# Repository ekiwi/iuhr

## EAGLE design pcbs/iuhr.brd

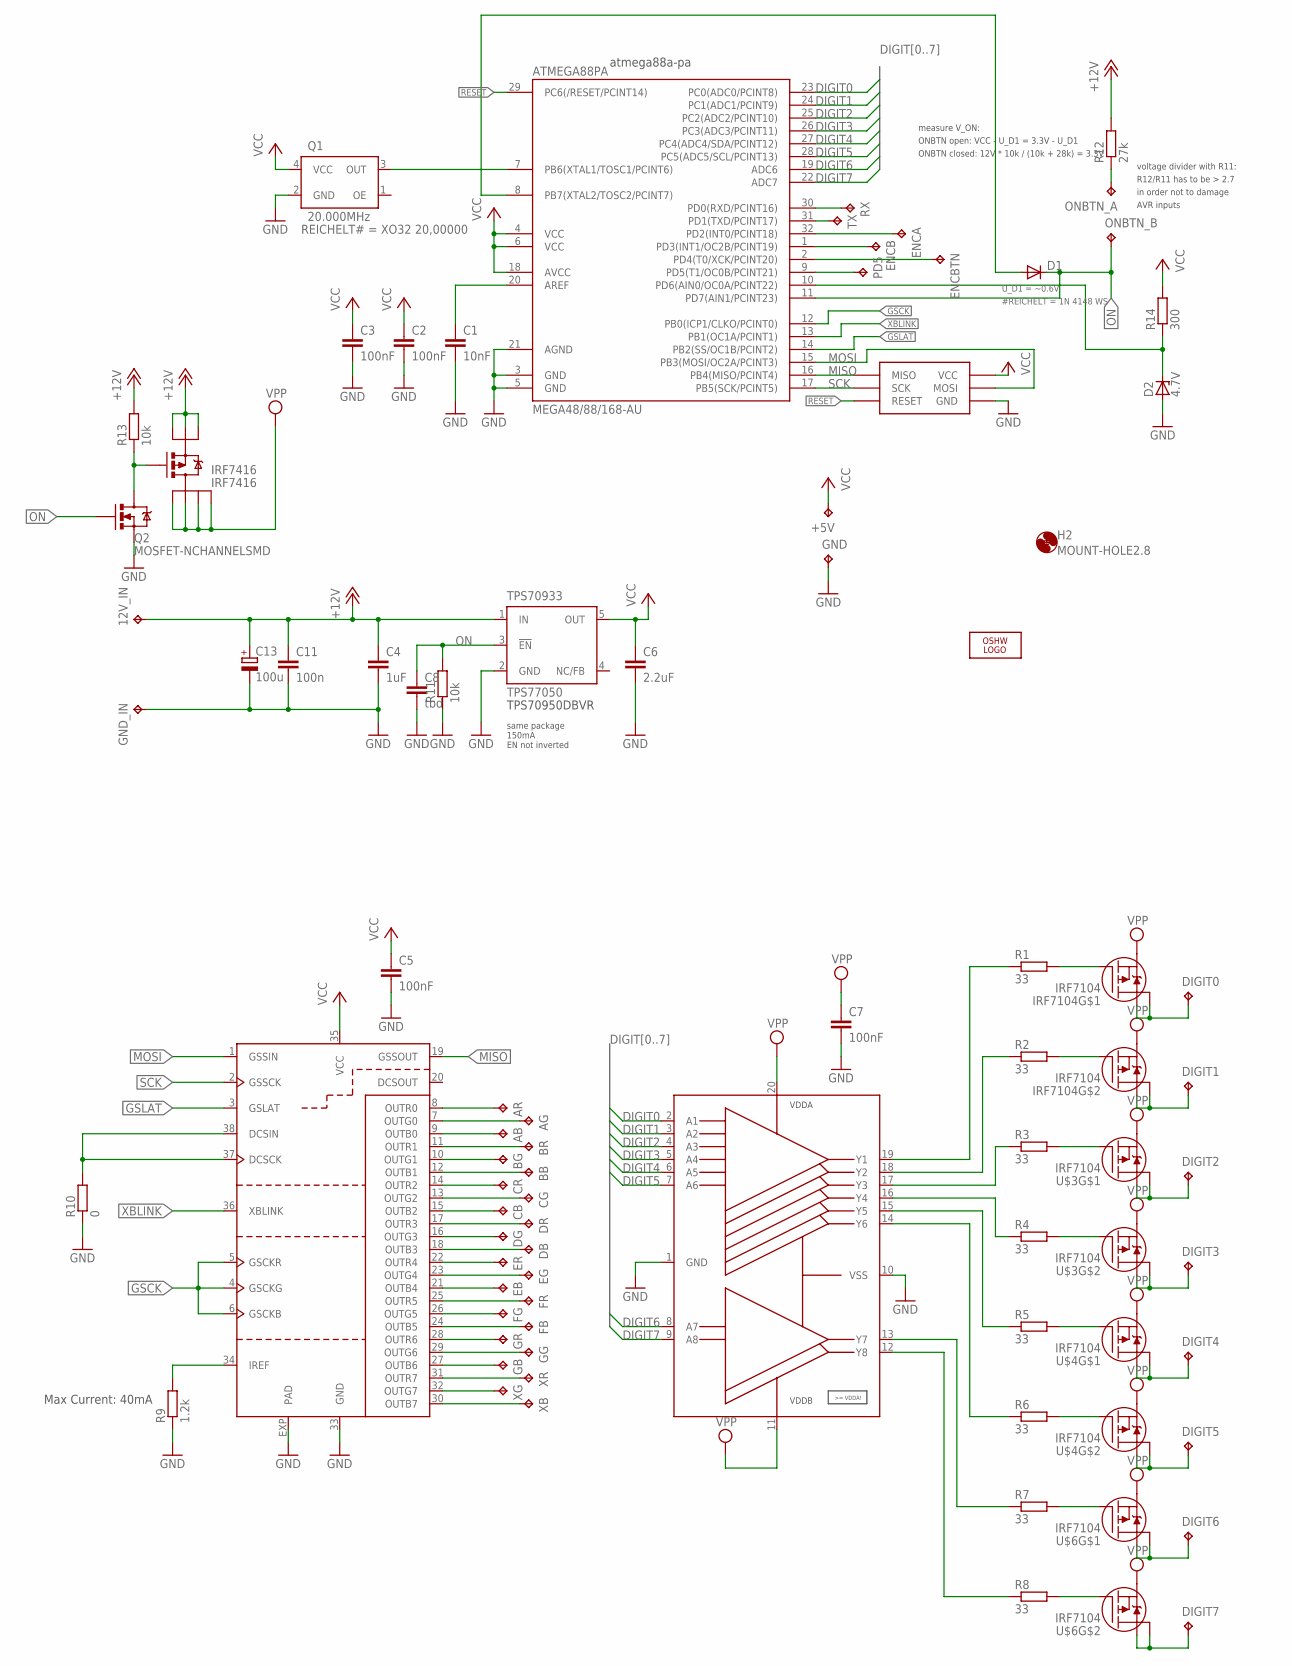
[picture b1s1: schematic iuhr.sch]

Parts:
12V_IN: TPTP20SQ; TP20SQ
+5V: TPTP15SQ; TP15SQ
AB: TPTP15SQ; TP15SQ
ADG3123: ADG3123BRUZ; TSSOP20
AG: TPTP15SQ; TP15SQ
AR: TPTP15SQ; TP15SQ
ATMEGA88PA: MEGA48/88/168-AU; TQFP32-08
BB: TPTP15SQ; TP15SQ
BG: TPTP15SQ; TP15SQ
BR: TPTP15SQ; TP15SQ
C1: 10nF; C0603
C2, C3, C5, C7: 100nF; C0603
C4: 1uF; C0805
C6: 2.2uF; C0805
C8: tbd; C0603
C11: 100n; C0603
C13: 100u; PANASONIC_E
CB: TPTP15SQ; TP15SQ
CG: TPTP15SQ; TP15SQ
CR: TPTP15SQ; TP15SQ
D1: DIODE-SOD323-R; SOD323-R
D2: 4.7V; SOT23
DB: TPTP15SQ; TP15SQ
DG: TPTP15SQ; TP15SQ
DIGIT0, DIGIT1, DIGIT2, DIGIT3, DIGIT4, DIGIT5, DIGIT6, DIGIT7: TPTP20SQ; TP20SQ
DR: TPTP15SQ; TP15SQ
EB: TPTP15SQ; TP15SQ
EG: TPTP15SQ; TP15SQ
ENCA: TPTP15SQ; TP15SQ
ENCB: TPTP15SQ; TP15SQ
ENCBTN: TPTP15SQ; TP15SQ
ER: TPTP15SQ; TP15SQ
FB: TPTP15SQ; TP15SQ
FG: TPTP15SQ; TP15SQ
FR: TPTP15SQ; TP15SQ
GB: TPTP15SQ; TP15SQ
GG: TPTP15SQ; TP15SQ
GND: TPTP15SQ; TP15SQ
GND_IN: TPTP20SQ; TP20SQ
GR: TPTP15SQ; TP15SQ
H2: MOUNT-HOLE2.8; 2,8
IRF7104: IRF7104; SO8-2
IRF7416: IRF7416; SO8-2
LOGO1: OSHW_LOGO_8MILX0200-NT; OSHW_8X200_NOTEXT
ONBTN_A: TPTP15SQ; TP15SQ
ONBTN_B: TPTP15SQ; TP15SQ
PD5: TPTP15SQ; TP15SQ
Q1: 20.000MHz; XO32
Q2: MOSFET-NCHANNELSMD; SOT23-3
R1, R2, R3, R4, R5, R6, R7, R8: 33; R0603
R9: 1.2k; R0603
R10: 0; R0603
R11, R13: 10k; R0603
R12: 27k; R0603
R14: 300; R0603
RX: TPTP15SQ; TP15SQ
TLC5951: TLC5951; HTSSOP38DAP
TPS70933: TPS77050; SOT23-DBV
TX: TPTP15SQ; TP15SQ
U$3, U$4, U$6: IRF7104; SO8-2
U$5: ISP_SPECIALS; ISP_RM2_00_STRAIGHT
XB: TPTP15SQ; TP15SQ
XG: TPTP15SQ; TP15SQ
XR: TPTP15SQ; TP15SQ

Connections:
+12V: 12V_IN.TP, C4.1, C11.1, C13.+, IRF7416.1 (S), IRF7416.2 (S1), IRF7416.3 (S2), R12.2, R13.2, TPS70933.1 (IN)
CLK_STM: ATMEGA88PA.7 (PB6(XTAL1/TOSC1/PCINT6)), Q1.3 (OUT)
DIGIT0: ADG3123.2 (A1), ATMEGA88PA.23 (PC0(ADC0/PCINT8))
DIGIT1: ADG3123.3 (A2), ATMEGA88PA.24 (PC1(ADC1/PCINT9))
DIGIT2: ADG3123.4 (A3), ATMEGA88PA.25 (PC2(ADC2/PCINT10))
DIGIT3: ADG3123.5 (A4), ATMEGA88PA.26 (PC3(ADC3/PCINT11))
DIGIT4: ADG3123.6 (A5), ATMEGA88PA.27 (PC4(ADC4/SDA/PCINT12))
DIGIT5: ADG3123.7 (A6), ATMEGA88PA.28 (PC5(ADC5/SCL/PCINT13))
DIGIT6: ADG3123.8 (A7), ATMEGA88PA.19 (ADC6)
DIGIT7: ADG3123.9 (A8), ATMEGA88PA.22 (ADC7)
GND: ADG3123.1 (GND), ADG3123.10 (VSS), ATMEGA88PA.3 (GND), ATMEGA88PA.5 (GND), ATMEGA88PA.21 (AGND), C1.2, C2.2, C3.2, C4.2, C5.2, C6.2, C7.2, C8.2, C11.2, C13.-, D2.1 (A), GND.TP, GND_IN.TP, Q1.2 (GND), Q2.2 (S), R9.1, R10.1, R11.1, TLC5951.33 (GND), TLC5951.EXP (PAD), TPS70933.2 (GND), U$5.VCC (GND)
GSCK: ATMEGA88PA.12 (PB0(ICP1/CLKO/PCINT0)), TLC5951.4 (GSCKG), TLC5951.5 (GSCKR), TLC5951.6 (GSCKB)
GSLAT: ATMEGA88PA.14 (PB2(SS/OC1B/PCINT2)), TLC5951.3 (GSLAT)
MISO: ATMEGA88PA.16 (PB4(MISO/PCINT4)), TLC5951.19 (GSSOUT), U$5.RESET (MISO)
MOSI: ATMEGA88PA.15 (PB3(MOSI/OC2A/PCINT3)), TLC5951.1 (GSSIN), U$5.MOSI
unnamed: AR.TP, TLC5951.8 (OUTR0)
unnamed: ATMEGA88PA.20 (AREF), C1.1
unnamed: AG.TP, TLC5951.7 (OUTG0)
unnamed: AB.TP, TLC5951.9 (OUTB0)
unnamed: BR.TP, TLC5951.11 (OUTR1)
unnamed: BG.TP, TLC5951.10 (OUTG1)
unnamed: ATMEGA88PA.30 (PD0(RXD/PCINT16)), RX.TP
unnamed: BB.TP, TLC5951.12 (OUTB1)
unnamed: CR.TP, TLC5951.14 (OUTR2)
unnamed: CG.TP, TLC5951.13 (OUTG2)
unnamed: CB.TP, TLC5951.15 (OUTB2)
unnamed: ATMEGA88PA.31 (PD1(TXD/PCINT17)), TX.TP
unnamed: DR.TP, TLC5951.17 (OUTR3)
unnamed: DG.TP, TLC5951.16 (OUTG3)
unnamed: DB.TP, TLC5951.18 (OUTB3)
unnamed: ER.TP, TLC5951.22 (OUTR4)
unnamed: EG.TP, TLC5951.23 (OUTG4)
unnamed: EB.TP, TLC5951.21 (OUTB4)
unnamed: FR.TP, TLC5951.25 (OUTR5)
unnamed: FG.TP, TLC5951.26 (OUTG5)
unnamed: ATMEGA88PA.32 (PD2(INT0/PCINT18)), ENCA.TP
unnamed: FB.TP, TLC5951.24 (OUTB5)
unnamed: GR.TP, TLC5951.28 (OUTR6)
unnamed: GG.TP, TLC5951.29 (OUTG6)
unnamed: GB.TP, TLC5951.27 (OUTB6)
unnamed: TLC5951.31 (OUTR7), XR.TP
unnamed: TLC5951.32 (OUTG7), XG.TP
unnamed: TLC5951.30 (OUTB7), XB.TP
unnamed: DIGIT0.TP, IRF7104.7 (D), IRF7104.8 (D)
unnamed: DIGIT1.TP, IRF7104.5 (D), IRF7104.6 (D)
unnamed: IRF7104.2 (G), R1.2
unnamed: IRF7104.4 (G), R2.2
unnamed: ADG3123.19 (Y1), R1.1
unnamed: DIGIT6.TP, U$6.7 (D), U$6.8 (D)
unnamed: DIGIT2.TP, U$3.7 (D), U$3.8 (D)
unnamed: DIGIT3.TP, U$3.5 (D), U$3.6 (D)
unnamed: R3.2, U$3.2 (G)
unnamed: R4.2, U$3.4 (G)
unnamed: ADG3123.17 (Y3), R3.1
unnamed: ADG3123.16 (Y4), R4.1
unnamed: DIGIT4.TP, U$4.7 (D), U$4.8 (D)
unnamed: DIGIT5.TP, U$4.5 (D), U$4.6 (D)
unnamed: R5.2, U$4.2 (G)
unnamed: R6.2, U$4.4 (G)
unnamed: ADG3123.15 (Y5), R5.1
unnamed: ADG3123.14 (Y6), R6.1
unnamed: ADG3123.18 (Y2), R2.1
unnamed: DIGIT7.TP, U$6.5 (D), U$6.6 (D)
unnamed: R7.2, U$6.2 (G)
unnamed: R8.2, U$6.4 (G)
unnamed: ADG3123.13 (Y7), R7.1
unnamed: ADG3123.12 (Y8), R8.1
unnamed: ATMEGA88PA.1 (PD3(INT1/OC2B/PCINT19)), ENCB.TP
unnamed: ATMEGA88PA.2 (PD4(T0/XCK/PCINT20)), ENCBTN.TP
unnamed: R9.2, TLC5951.34 (IREF)
unnamed: ATMEGA88PA.9 (PD5(T1/OC0B/PCINT21)), PD5.TP
unnamed: ATMEGA88PA.10 (PD6(AIN0/OC0A/PCINT22)), D2.3 (C), R14.1
unnamed: ATMEGA88PA.8 (PB7(XTAL2/TOSC2/PCINT7)), D1.A
unnamed: ONBTN_A.TP, R12.1
unnamed: R10.2, TLC5951.37 (DCSCK), TLC5951.38 (DCSIN)
unnamed: IRF7416.4 (G), Q2.3 (D), R13.1
ON: ATMEGA88PA.11 (PD7(AIN1/PCINT23)), C8.1, D1.C, ONBTN_B.TP, Q2.1 (G), R11.2, TPS70933.3 (!EN)
RESET: ATMEGA88PA.29 (PC6(/RESET/PCINT14)), U$5.MISO (RESET)
SCK: ATMEGA88PA.17 (PB5(SCK/PCINT5)), TLC5951.2 (GSSCK), U$5.SCK
VCC: +5V.TP, ATMEGA88PA.4 (VCC), ATMEGA88PA.6 (VCC), ATMEGA88PA.18 (AVCC), C2.1, C3.1, C5.1, C6.1, Q1.4 (VCC), R14.2, TLC5951.35 (VCC), TPS70933.5 (OUT), U$5.GND (VCC)
VPP: ADG3123.11 (VDDB), ADG3123.20 (VDDA), C7.1, IRF7104.1 (S), IRF7104.3 (S), IRF7416.5 (D3), IRF7416.6 (D2), IRF7416.7 (D1), IRF7416.8 (D), U$3.1 (S), U$3.3 (S), U$4.1 (S), U$4.3 (S), U$6.1 (S), U$6.3 (S)
XBLINK: ATMEGA88PA.13 (PB1(OC1A/PCINT1)), TLC5951.36 (XBLINK)

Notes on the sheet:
atmega88a-pa
Max Current: 40mA
TPS70950DBVR
same package 150mA EN not inverted
measure V_ON:
ONBTN open: VCC - U_D1 = 3.3V - U_D1
ONBTN closed: 12V * 10k / (10k + 28k) = 3.3V
voltage divider with R11:
R12/R11 has to be > 2.7
in order not to damage
AVR inputs

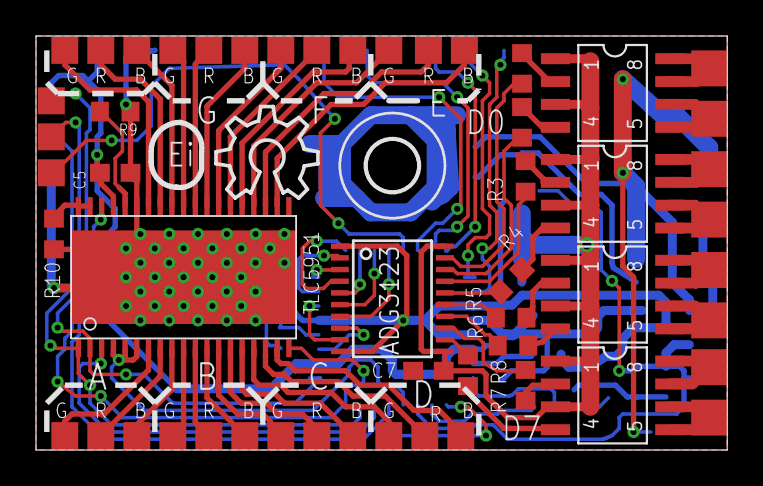
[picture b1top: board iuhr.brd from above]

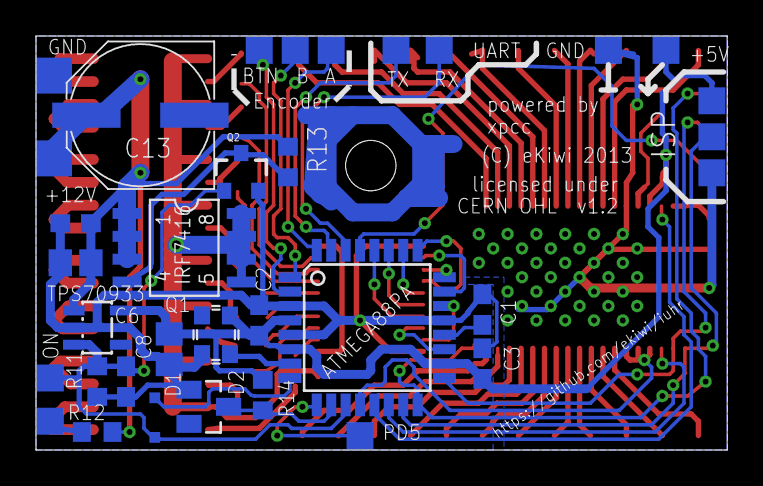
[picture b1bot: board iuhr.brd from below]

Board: 2 copper layers, 38.4 x 23.0 mm, 84 parts (31 on the bottom side), 82 nets.

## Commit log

2013-11-16 iUhr: add initial schematic
2013-11-16 Started board layout
2013-11-17 No Airwires. No unapproved DRC Errors.
2013-11-17 Add ground plane and thermal vias.
2013-11-17 Improved Silkscreen.
2013-11-17 Break out unused pins
2013-11-17 Further improve silkscreen.
2013-11-17 VCC: 3.3V -> 5V; add cap for adg3123
2013-11-17 Power On: add cap and series resistor for button.
2013-11-17 Add p-channel mosfet to be able to shut off 12V part.
    TODO: find space on board
2013-11-18 correct power-on button and add detection
    ToDo: - reassign DIGIT6
    - layout for this commit
2013-11-18 Can now use "ON" Switch to turn board off
2013-11-19 Swap functionality of PB7 and PD5
2013-11-19 Improved GND connectivity
2013-11-19 Add GND and +5V breakout pads.
2013-11-19 Improve silkscreen.
2013-11-20 Separate logic and power ground.
2013-11-20 Small silk screen fixes.
2013-12-15 Drawings: add dxf
2013-12-17 Software: staying alive and Uart
2013-12-20 some TLC code
2013-12-21 sound and light
2014-04-16 Use different programmer
2014-04-16 TLC: fix incorrect shift
2014-04-16 Go trough rows. WARNING: untested
2014-12-14 Tlc: port to latest xpcc
2014-12-14 Main: leds are glowing!!
2014-12-14 Pcb: digital logic needs to run on 3.3V
    The osicallator only works with 3.3V
    (which I realized one year after designing this...)
    thus we will run the whole logic with 3.3V
    which works for all chips except for the
    atmega which is now a little bit overclocked.
    It still seems to work, but is not recommended
2014-12-14 Add displaty class
2014-12-14 Display: actually there are three color channels
2014-12-15 Latest xpcc develop
    There is still a patch for
    Spi missing though.

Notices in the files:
pcbs/iuhr.brd:
licensed under
CERN OHL  v1.2
parts and their libraries:
irf-2: Copyright & License
This library is licensed under the General Public License, Version 2.
More Information about the General Public License is available at http://www.gnu.org/copyleft/gpl.html.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
